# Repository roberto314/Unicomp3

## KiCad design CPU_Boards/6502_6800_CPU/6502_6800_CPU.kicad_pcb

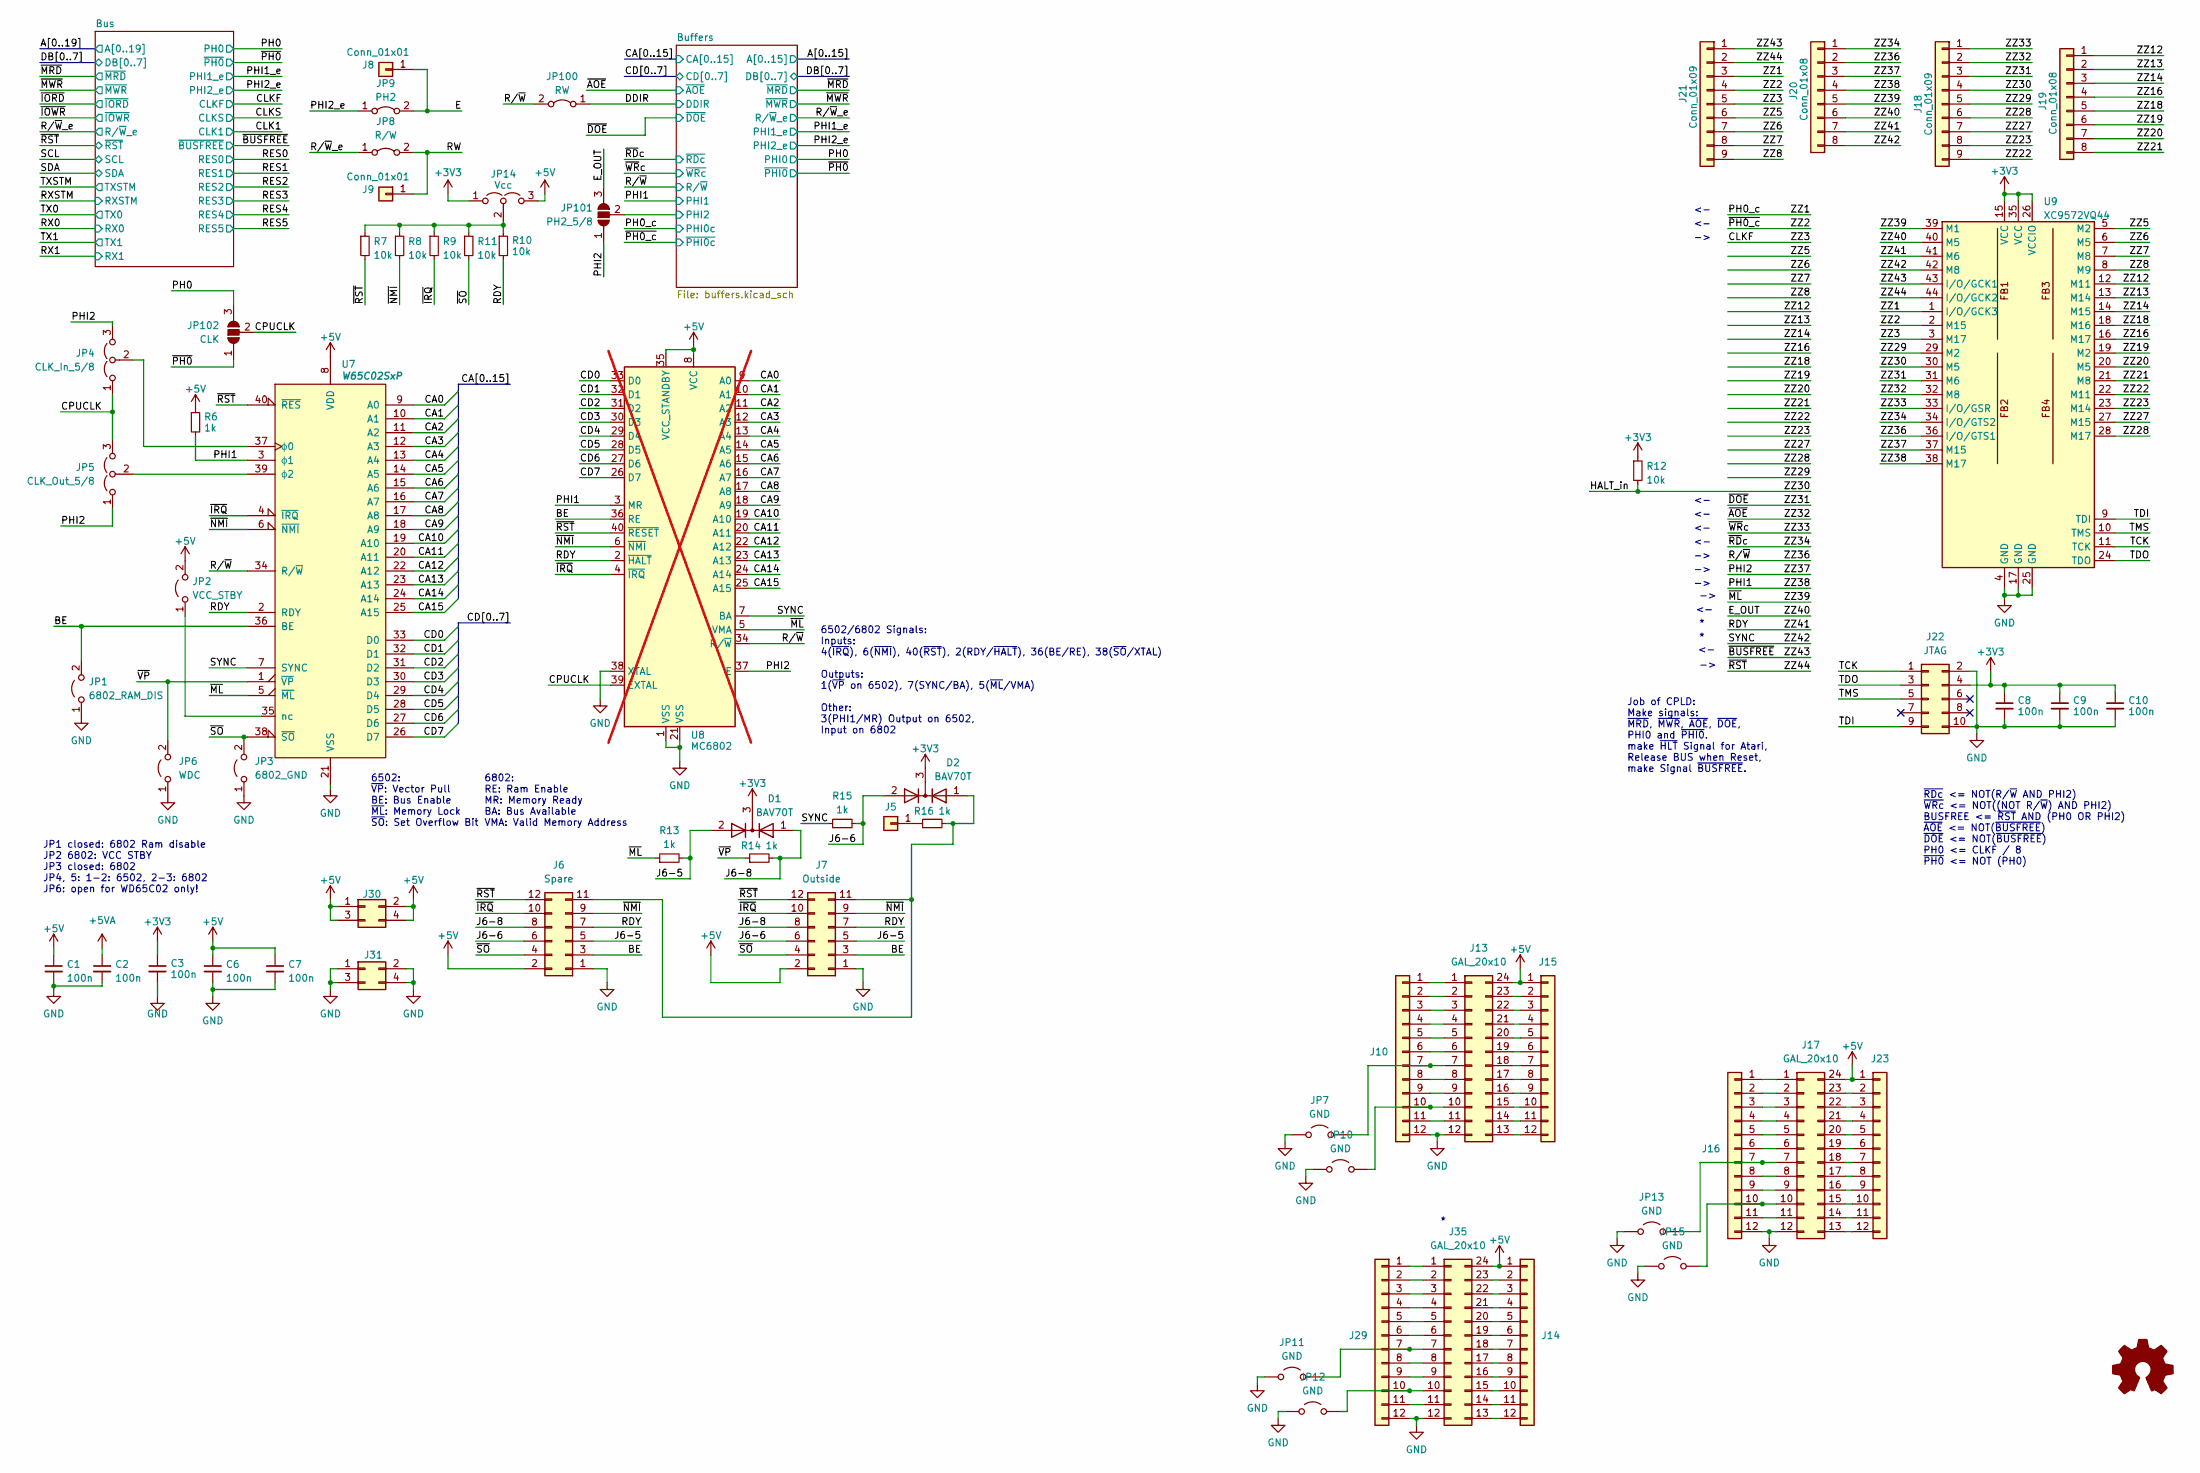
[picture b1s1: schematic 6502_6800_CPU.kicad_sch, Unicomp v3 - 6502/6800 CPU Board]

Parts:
C1, C2, C3, C6, C7, C8, C9, C10: 100n; C_1206_3216Metric
D1, D2: BAV70T; SOT-23_Handsoldering
J5: Conn_01x01; PinSocket_1x01_P1.27mm_Vertical
J6: Spare; PinHeader_2x06_P2.54mm_Vertical
J7: Outside; PinHeader_2x06_P2.54mm_Horizontal
J8, J9: Conn_01x01; PinHeader_1x01_P2.00mm_Vertical
J10, J14, J15, J16, J23, J29: Conn_01x12; PinSocket_1x12_P2.54mm_Vertical
J13, J17, J35: GAL_20x10; DIP-24_W7.62mm
J18, J21: Conn_01x09; PinHeader_1x09_P2.54mm_Vertical
J19, J20: Conn_01x08; PinHeader_1x08_P2.54mm_Vertical
J22: JTAG; PinHeader_2x05_P2.54mm_Horizontal
J30, J31: Conn_02x02_Odd_Even; PinSocket_2x02_P2.54mm_Vertical
JP1: 6802_RAM_DIS; SolderJumper-2_P1.3mm_Open_RoundedPad1.0x1.5mm
JP2: VCC_STBY; SolderJumper-2_P1.3mm_Open_RoundedPad1.0x1.5mm
JP3: 6802_GND; SolderJumper-2_P1.3mm_Open_RoundedPad1.0x1.5mm
JP4: CLK_In_5/8; SolderJumper-3_P1.3mm_Open_Pad1.0x1.5mm_NumberLabels
JP5: CLK_Out_5/8; SolderJumper-3_P1.3mm_Open_Pad1.0x1.5mm_NumberLabels
JP6: WDC; SolderJumper-2_P1.3mm_Open_RoundedPad1.0x1.5mm
JP7, JP10, JP11, JP12, JP13, JP15: GND; SolderJumper-2_P1.3mm_Open_RoundedPad1.0x1.5mm
JP8: R/W; SolderJumper-2_P1.3mm_Bridged_RoundedPad1.0x1.5mm
JP9: PH2; SolderJumper-2_P1.3mm_Bridged_RoundedPad1.0x1.5mm
JP14: Vcc; SolderJumper-3_P1.3mm_Open_RoundedPad1.0x1.5mm_NumberLabels
JP100: RW; SolderJumper-2_P1.3mm_Bridged_RoundedPad1.0x1.5mm
JP101: PH2_5/8; SolderJumper-3_P1.3mm_Open_RoundedPad1.0x1.5mm_NumberLabels
JP102: CLK; SolderJumper-3_P1.3mm_Open_RoundedPad1.0x1.5mm_NumberLabels
R6, R13, R14, R15, R16: 1k; R_1206_3216Metric_Pad1.30x1.75mm_HandSolder
R7, R8, R9, R10, R11, R12: 10k; R_1206_3216Metric_Pad1.30x1.75mm_HandSolder
U7: W65C02SxP; DIP-40_W15.24mm_Socket_LongPads
U8: MC6802; DIP-40_W15.24mm; not fitted
U9: XC9572VQ44; TQFP-44_10x10mm_P0.8mm

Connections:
+3V3: C3.1, C8.1, C9.1, C10.1, D1.3 (K), D2.3 (K), J22.4, JP14.1 (A), R12.1, U9.15 (VCC), U9.26 (VCCIO), U9.35 (VCC); also elsewhere on the board
+5V: C1.1, C6.1, C7.1, J6.2, J7.2, J13.24, J14.1, J15.1, J17.24, J23.1, J30.1, J30.2, J30.3, J30.4, J35.24, JP2.2 (B), JP14.3 (B), R6.1, U7.8 (VDD), U8.8 (VCC), U8.35 (VCC_STANDBY); also elsewhere on the board
+5VA: C2.1; also elsewhere on the board
/BE: J6.3, J7.3, JP1.2 (B), U7.36 (BE), U8.36 (RE)
/Buffers/PHI2: JP101.2 (C); also elsewhere on the board
/CA0: U7.9 (A0), U8.9 (A0); also elsewhere on the board
/CA1: U7.10 (A1), U8.10 (A1); also elsewhere on the board
/CA2: U7.11 (A2), U8.11 (A2); also elsewhere on the board
/CA3: U7.12 (A3), U8.12 (A3); also elsewhere on the board
/CA4: U7.13 (A4), U8.13 (A4); also elsewhere on the board
/CA5: U7.14 (A5), U8.14 (A5); also elsewhere on the board
/CA6: U7.15 (A6), U8.15 (A6); also elsewhere on the board
/CA7: U7.16 (A7), U8.16 (A7); also elsewhere on the board
/CA8: U7.17 (A8), U8.17 (A8); also elsewhere on the board
/CA9: U7.18 (A9), U8.18 (A9); also elsewhere on the board
/CA10: U7.19 (A10), U8.19 (A10); also elsewhere on the board
/CA11: U7.20 (A11), U8.20 (A11); also elsewhere on the board
/CA12: U7.22 (A12), U8.22 (A12); also elsewhere on the board
/CA13: U7.23 (A13), U8.23 (A13); also elsewhere on the board
/CA14: U7.24 (A14), U8.24 (A14); also elsewhere on the board
/CA15: U7.25 (A15), U8.25 (A15); also elsewhere on the board
/CD0: U7.33 (D0), U8.33 (D0); also elsewhere on the board
/CD1: U7.32 (D1), U8.32 (D1); also elsewhere on the board
/CD2: U7.31 (D2), U8.31 (D2); also elsewhere on the board
/CD3: U7.30 (D3), U8.30 (D3); also elsewhere on the board
/CD4: U7.29 (D4), U8.29 (D4); also elsewhere on the board
/CD5: U7.28 (D5), U8.28 (D5); also elsewhere on the board
/CD6: U7.27 (D6), U8.27 (D6); also elsewhere on the board
/CD7: U7.26 (D7), U8.26 (D7); also elsewhere on the board
/CLKF: J21.5, U9.3 (M17); also elsewhere on the board
/CPUCLK: JP4.1 (A), JP5.3 (B), JP102.2 (C), U8.39 (EXTAL)
/DDIR: JP100.1 (A); also elsewhere on the board
/E: J8.1, JP9.2 (B)
/E_OUT: J20.6, JP101.3 (B), U9.40 (M5)
/HALT_in: J18.4, R12.2, U9.30 (M5)
/J6-5: D1.2 (A), J6.5, J7.5, R13.2
/J6-6: D2.2 (A), J6.6, J7.6, R15.2
/J6-8: D1.1 (A), J6.8, J7.8, R14.2
/PH0: JP102.3 (B); also elsewhere on the board
/PH0_c: J21.3, U9.1 (I/O/GCK3); also elsewhere on the board
/PHI1: J20.4, R6.2, U7.3 (ϕ1), U8.3 (MR), U9.38 (M17); also elsewhere on the board
/PHI2: J20.3, JP4.3 (B), JP5.1 (A), JP101.1 (A), U8.37 (E), U9.37 (M15)
/PHI2_e: JP9.1 (A); also elsewhere on the board
/RDY: J6.7, J7.7, J20.7, R10.2, U7.2 (RDY), U8.2 (~HALT), U9.41 (M6)
/RW: J9.1, JP8.2 (B)
/R/~W: J20.2, JP100.2 (B), U7.34 (R/~W), U8.34 (R/~W), U9.36 (I/O/GTS1); also elsewhere on the board
/R/~W_e: JP8.1 (A); also elsewhere on the board
/SYNC: J20.8, R15.1, U7.7 (SYNC), U8.7 (BA), U9.42 (M8)
/TCK: J22.1, U9.11 (TCK)
/TDI: J22.9, U9.9 (TDI)
/TDO: J22.3, U9.24 (TDO)
/TMS: J22.5, U9.10 (TMS)
/ZZ2: J21.4, U9.2 (M15); also elsewhere on the board
/ZZ5: J21.6, U9.5 (M2)
/ZZ6: J21.7, U9.6 (M5)
/ZZ7: J21.8, U9.7 (M8)
/ZZ8: J21.9, U9.8 (M9)
/ZZ12: J19.1, U9.12 (M11)
/ZZ13: J19.2, U9.13 (M14)
/ZZ14: J19.3, U9.14 (M15)
/ZZ16: J19.4, U9.16 (M17)
/ZZ18: J19.5, U9.18 (M16)
/ZZ19: J19.6, U9.19 (M2)
/ZZ20: J19.7, U9.20 (M5)
/ZZ21: J19.8, U9.21 (M8)
/ZZ22: J18.9, U9.22 (M11)
/ZZ23: J18.8, U9.23 (M14)
/ZZ27: J18.7, U9.27 (M15)
/ZZ28: J18.6, U9.28 (M17)
/ZZ29: J18.5, U9.29 (M2)
/ZZ31: J18.3, U9.31 (M6); also elsewhere on the board
/ZZ32: J18.2, U9.32 (M8); also elsewhere on the board
/ZZ33: J18.1, U9.33 (I/O/GSR); also elsewhere on the board
/ZZ34: J20.1, U9.34 (I/O/GTS2); also elsewhere on the board
/ZZ39: J20.5, R13.1, U7.5 (~ML), U8.5 (VMA), U9.39 (M1)
/ZZ43: J21.1, U9.43 (I/O/GCK1); also elsewhere on the board
/ZZ44: J6.12, J7.12, J21.2, R7.2, U7.40 (~RES), U8.40 (~RESET), U9.44 (I/O/GCK2); also elsewhere on the board
/~IRQ: J6.10, J7.10, R9.2, U7.4 (~IRQ), U8.4 (~IRQ)
/~NMI: J6.9, J7.9, R8.2, U7.6 (~NMI), U8.6 (~NMI)
/~PH0: JP102.1 (A); also elsewhere on the board
/~SO: J6.4, J7.4, JP3.2 (B), R11.2, U7.38 (~SO)
/~VP: JP6.2 (B), R14.1, U7.1 (~VP)
GND: C1.2, C2.2, C3.2, C6.2, C7.2, C8.2, C9.2, C10.2, J6.1, J7.1, J10.12, J13.12, J16.12, J17.12, J22.2, J22.10, J29.12, J31.1, J31.2, J31.3, J31.4, J35.12, JP1.1 (A), JP3.1 (A), JP6.1 (A), JP7.1 (A), JP10.1 (A), JP11.1 (A), JP12.1 (A), JP13.1 (A), JP15.1 (A), U7.21 (VSS), U8.1 (VSS), U8.21 (VSS), U8.38 (XTAL), U9.4 (GND), U9.17 (GND), U9.25 (GND); also elsewhere on the board
unnamed: J5.1, R16.1
unnamed: D2.1 (A), J6.11, J7.11, R16.2
unnamed: J10.1, J13.1
unnamed: J10.2, J13.2
unnamed: J10.3, J13.3
unnamed: J10.4, J13.4
unnamed: J10.5, J13.5
unnamed: J10.6, J13.6
unnamed: J10.7, J13.7, JP7.2 (B)
unnamed: J10.8, J13.8
unnamed: J10.9, J13.9
unnamed: J10.10, J13.10, JP10.2 (B)
unnamed: J10.11, J13.11
unnamed: J13.13, J15.12
unnamed: J13.14, J15.11
unnamed: J13.15, J15.10
unnamed: J13.16, J15.9
unnamed: J13.17, J15.8
unnamed: J13.18, J15.7
unnamed: J13.19, J15.6
unnamed: J13.20, J15.5
unnamed: J13.21, J15.4
unnamed: J13.22, J15.3
unnamed: J13.23, J15.2
unnamed: J14.2, J35.23
unnamed: J14.3, J35.22
unnamed: J14.4, J35.21
unnamed: J14.5, J35.20
unnamed: J14.6, J35.19
unnamed: J14.7, J35.18
unnamed: J14.8, J35.17
unnamed: J14.9, J35.16
unnamed: J14.10, J35.15
unnamed: J14.11, J35.14
unnamed: J14.12, J35.13
unnamed: J16.1, J17.1
unnamed: J16.2, J17.2
unnamed: J16.3, J17.3
unnamed: J16.4, J17.4
unnamed: J16.5, J17.5
unnamed: J16.6, J17.6
unnamed: J16.7, J17.7, JP13.2 (B)
unnamed: J16.8, J17.8
unnamed: J16.9, J17.9
unnamed: J16.10, J17.10, JP15.2 (B)
unnamed: J16.11, J17.11
unnamed: J17.13, J23.12
unnamed: J17.14, J23.11
unnamed: J17.15, J23.10
unnamed: J17.16, J23.9
unnamed: J17.17, J23.8
unnamed: J17.18, J23.7
unnamed: J17.19, J23.6
unnamed: J17.20, J23.5
unnamed: J17.21, J23.4
unnamed: J17.22, J23.3
unnamed: J17.23, J23.2
unnamed: J29.1, J35.1
unnamed: J29.2, J35.2
unnamed: J29.3, J35.3
unnamed: J29.4, J35.4
unnamed: J29.5, J35.5
unnamed: J29.6, J35.6
unnamed: J29.7, J35.7, JP11.2 (B)
unnamed: J29.8, J35.8
unnamed: J29.9, J35.9
unnamed: J29.10, J35.10, JP12.2 (B)
unnamed: J29.11, J35.11
unnamed: JP2.1 (A), U7.35 (nc)
unnamed: JP4.2 (C), U7.37 (ϕ0)
unnamed: JP5.2 (C), U7.39 (ϕ2)
unnamed: JP14.2 (C), R7.1, R8.1, R9.1, R10.1, R11.1

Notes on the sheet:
6502/6802 Signals: Inputs: 4(~{IRQ}), 6(~{NMI}), 40(~{RST}), 2(RDY/~{HALT}), 36(BE/RE), 38(~{SO}/XTAL) Outputs: 1(~{VP} on 6502), 7(SYNC/BA), 5(~{ML}/VMA) Other: 3(PHI1/MR) Output on 6502, Input on 6802
JP1 closed: 6802 Ram disable JP2 6802: VCC STBY JP3 closed: 6802 JP4, 5: 1-2: 6502, 2-3: 6802 JP6: open for WD65C02 only!
6502: ~{VP}: Vector Pull BE: Bus Enable ~{ML}: Memory Lock ~{SO}: Set Overflow Bit
Job of CPLD: Make signals: ~{MRD}, ~{MWR}, ~{AOE}, ~{DOE}, PHI0 and ~{PHI0}. make ~{HLT} Signal for Atari, Release BUS when Reset, make Signal ~{BUSFREE}.
~{RDc} <= NOT(R/~{W} AND PHI2) ~{WRc} <= NOT((NOT R/~{W}) AND PHI2) BUSFREE <= ~{RST} AND (PH0 OR PHI2) ~{AOE} <= NOT(~{BUSFREE}) ~{DOE} <= NOT(~{BUSFREE}) PH0 <= CLKF / 8 ~{PH0} <= NOT (PH0)
6802: RE: Ram Enable MR: Memory Ready BA: Bus Available VMA: Valid Memory Address

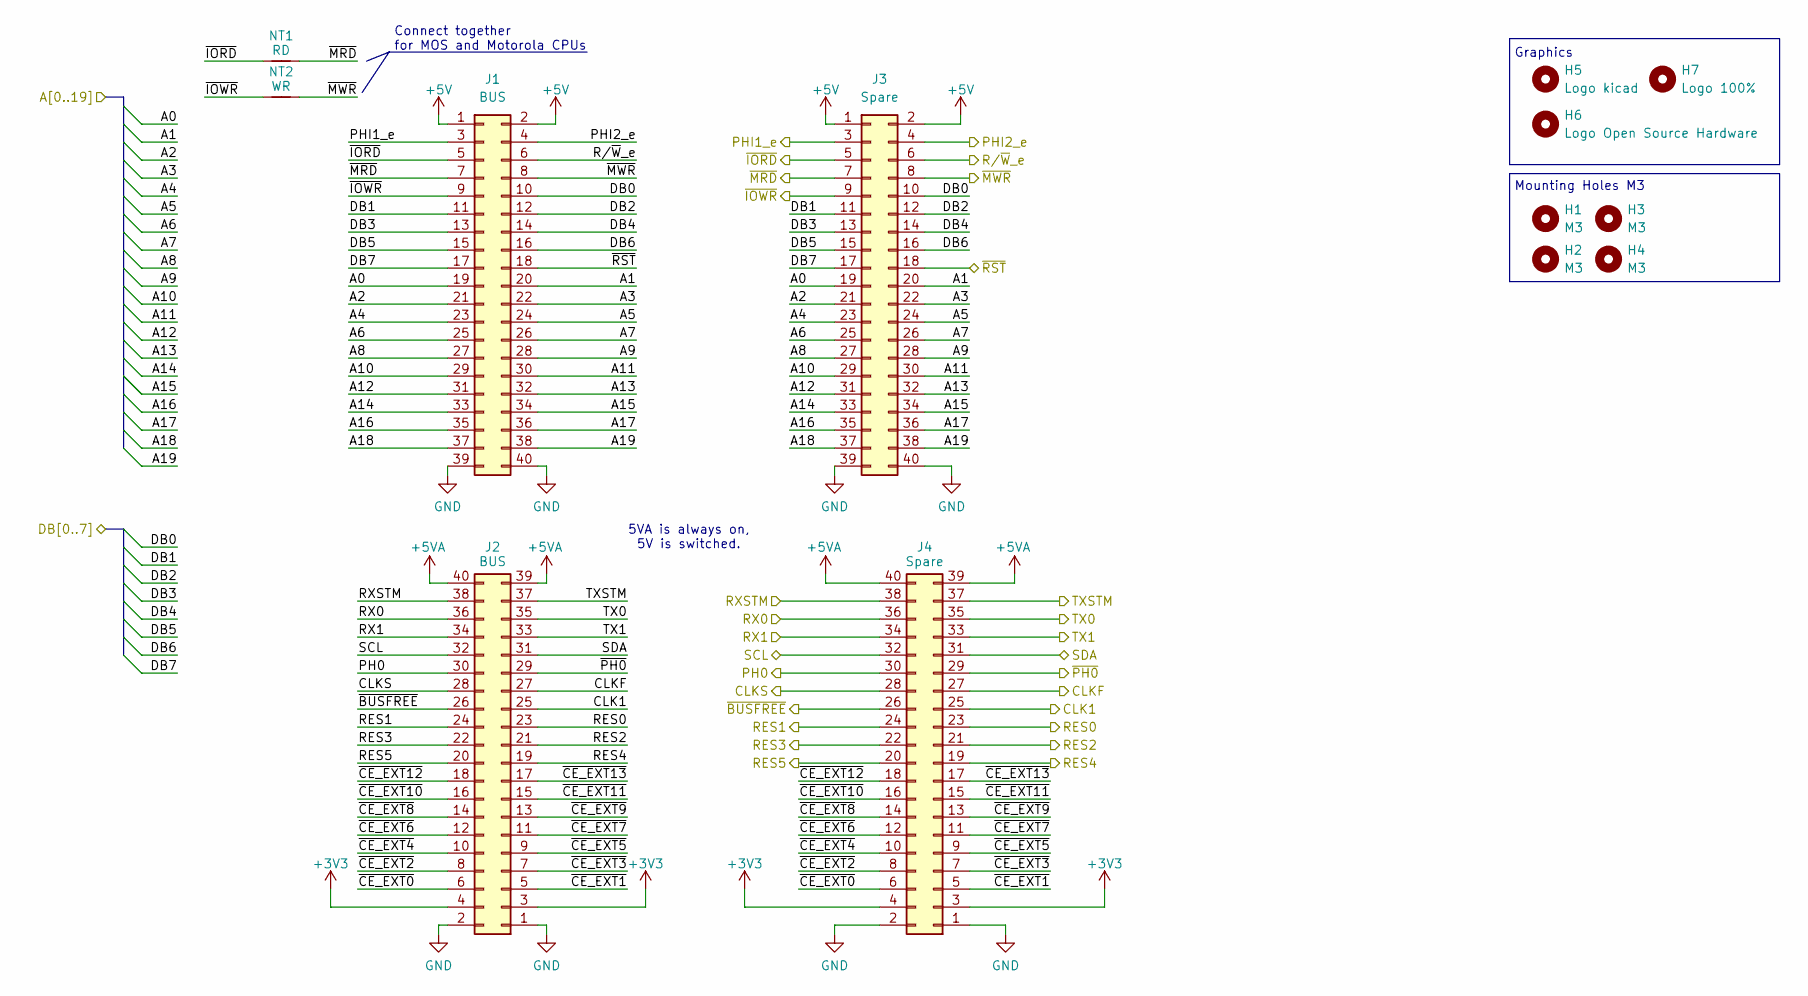
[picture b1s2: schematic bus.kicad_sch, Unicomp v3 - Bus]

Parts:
H1, H2, H3, H4: M3; MountingHole_3.2mm_M3
H5: Logo kicad; KiCad-Logo2_6mm_SilkScreen
H6: Logo Open Source Hardware; OSHW-Logo2_7.3x6mm_SilkScreen
H7: Logo 100%; Logo_100ProzentOffner_10x2.7mm
J1, J2: BUS; PinSocket_2x20_P2.54mm_Vertical
J3, J4: Spare; PinSocket_2x20_P2.54mm_Vertical
NT1: RD; NetTie-2_SMD_Pad0.5mm
NT2: WR; NetTie-2_SMD_Pad0.5mm

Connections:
+3V3: J2.3, J2.4, J4.3, J4.4; also elsewhere on the board
+5V: J1.1, J1.2, J3.1, J3.2; also elsewhere on the board
+5VA: J2.39, J2.40, J4.39, J4.40; also elsewhere on the board
/A0: J1.19, J3.19; also elsewhere on the board
/A1: J1.20, J3.20; also elsewhere on the board
/A2: J1.21, J3.21; also elsewhere on the board
/A3: J1.22, J3.22; also elsewhere on the board
/A4: J1.23, J3.23; also elsewhere on the board
/A5: J1.24, J3.24; also elsewhere on the board
/A6: J1.25, J3.25; also elsewhere on the board
/A7: J1.26, J3.26; also elsewhere on the board
/A8: J1.27, J3.27; also elsewhere on the board
/A9: J1.28, J3.28; also elsewhere on the board
/A10: J1.29, J3.29; also elsewhere on the board
/A11: J1.30, J3.30; also elsewhere on the board
/A12: J1.31, J3.31; also elsewhere on the board
/A13: J1.32, J3.32; also elsewhere on the board
/A14: J1.33, J3.33; also elsewhere on the board
/A15: J1.34, J3.34; also elsewhere on the board
/A16: J1.35, J3.35
/A17: J1.36, J3.36
/A18: J1.37, J3.37
/A19: J1.38, J3.38
/Bus/~CE_EXT0: J2.6, J4.6
/Bus/~CE_EXT1: J2.5, J4.5
/Bus/~CE_EXT2: J2.8, J4.8
/Bus/~CE_EXT3: J2.7, J4.7
/Bus/~CE_EXT4: J2.10, J4.10
/Bus/~CE_EXT5: J2.9, J4.9
/Bus/~CE_EXT6: J2.12, J4.12
/Bus/~CE_EXT7: J2.11, J4.11
/Bus/~CE_EXT8: J2.14, J4.14
/Bus/~CE_EXT9: J2.13, J4.13
/Bus/~CE_EXT10: J2.16, J4.16
/Bus/~CE_EXT11: J2.15, J4.15
/Bus/~CE_EXT12: J2.18, J4.18
/Bus/~CE_EXT13: J2.17, J4.17
/CLK1: J2.25, J4.25
/CLKF: J2.27, J4.27; also elsewhere on the board
/CLKS: J2.28, J4.28
/DB0: J1.10, J3.10; also elsewhere on the board
/DB1: J1.11, J3.11; also elsewhere on the board
/DB2: J1.12, J3.12; also elsewhere on the board
/DB3: J1.13, J3.13; also elsewhere on the board
/DB4: J1.14, J3.14; also elsewhere on the board
/DB5: J1.15, J3.15; also elsewhere on the board
/DB6: J1.16, J3.16; also elsewhere on the board
/DB7: J1.17, J3.17; also elsewhere on the board
/PH0: J2.30, J4.30; also elsewhere on the board
/PHI1_e: J1.3, J3.3; also elsewhere on the board
/PHI2_e: J1.4, J3.4; also elsewhere on the board
/RES0: J2.23, J4.23
/RES1: J2.24, J4.24
/RES2: J2.21, J4.21
/RES3: J2.22, J4.22
/RES4: J2.19, J4.19
/RES5: J2.20, J4.20
/RX0: J2.36, J4.36
/RX1: J2.34, J4.34
/RXSTM: J2.38, J4.38
/R/~W_e: J1.6, J3.6; also elsewhere on the board
/SCL: J2.32, J4.32
/SDA: J2.31, J4.31
/TX0: J2.35, J4.35
/TX1: J2.33, J4.33
/TXSTM: J2.37, J4.37
/ZZ43: J2.26, J4.26; also elsewhere on the board
/ZZ44: J1.18, J3.18; also elsewhere on the board
/~IORD: J1.5, J3.5, NT1.1
/~IOWR: J1.9, J3.9, NT2.1
/~MRD: J1.7, J3.7, NT1.2; also elsewhere on the board
/~MWR: J1.8, J3.8, NT2.2; also elsewhere on the board
/~PH0: J2.29, J4.29; also elsewhere on the board
GND: J1.39, J1.40, J2.1, J2.2, J3.39, J3.40, J4.1, J4.2; also elsewhere on the board

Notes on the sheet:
Graphics
Connect together for MOS and Motorola CPUs
5VA is always on, 5V is switched.
Mounting Holes M3

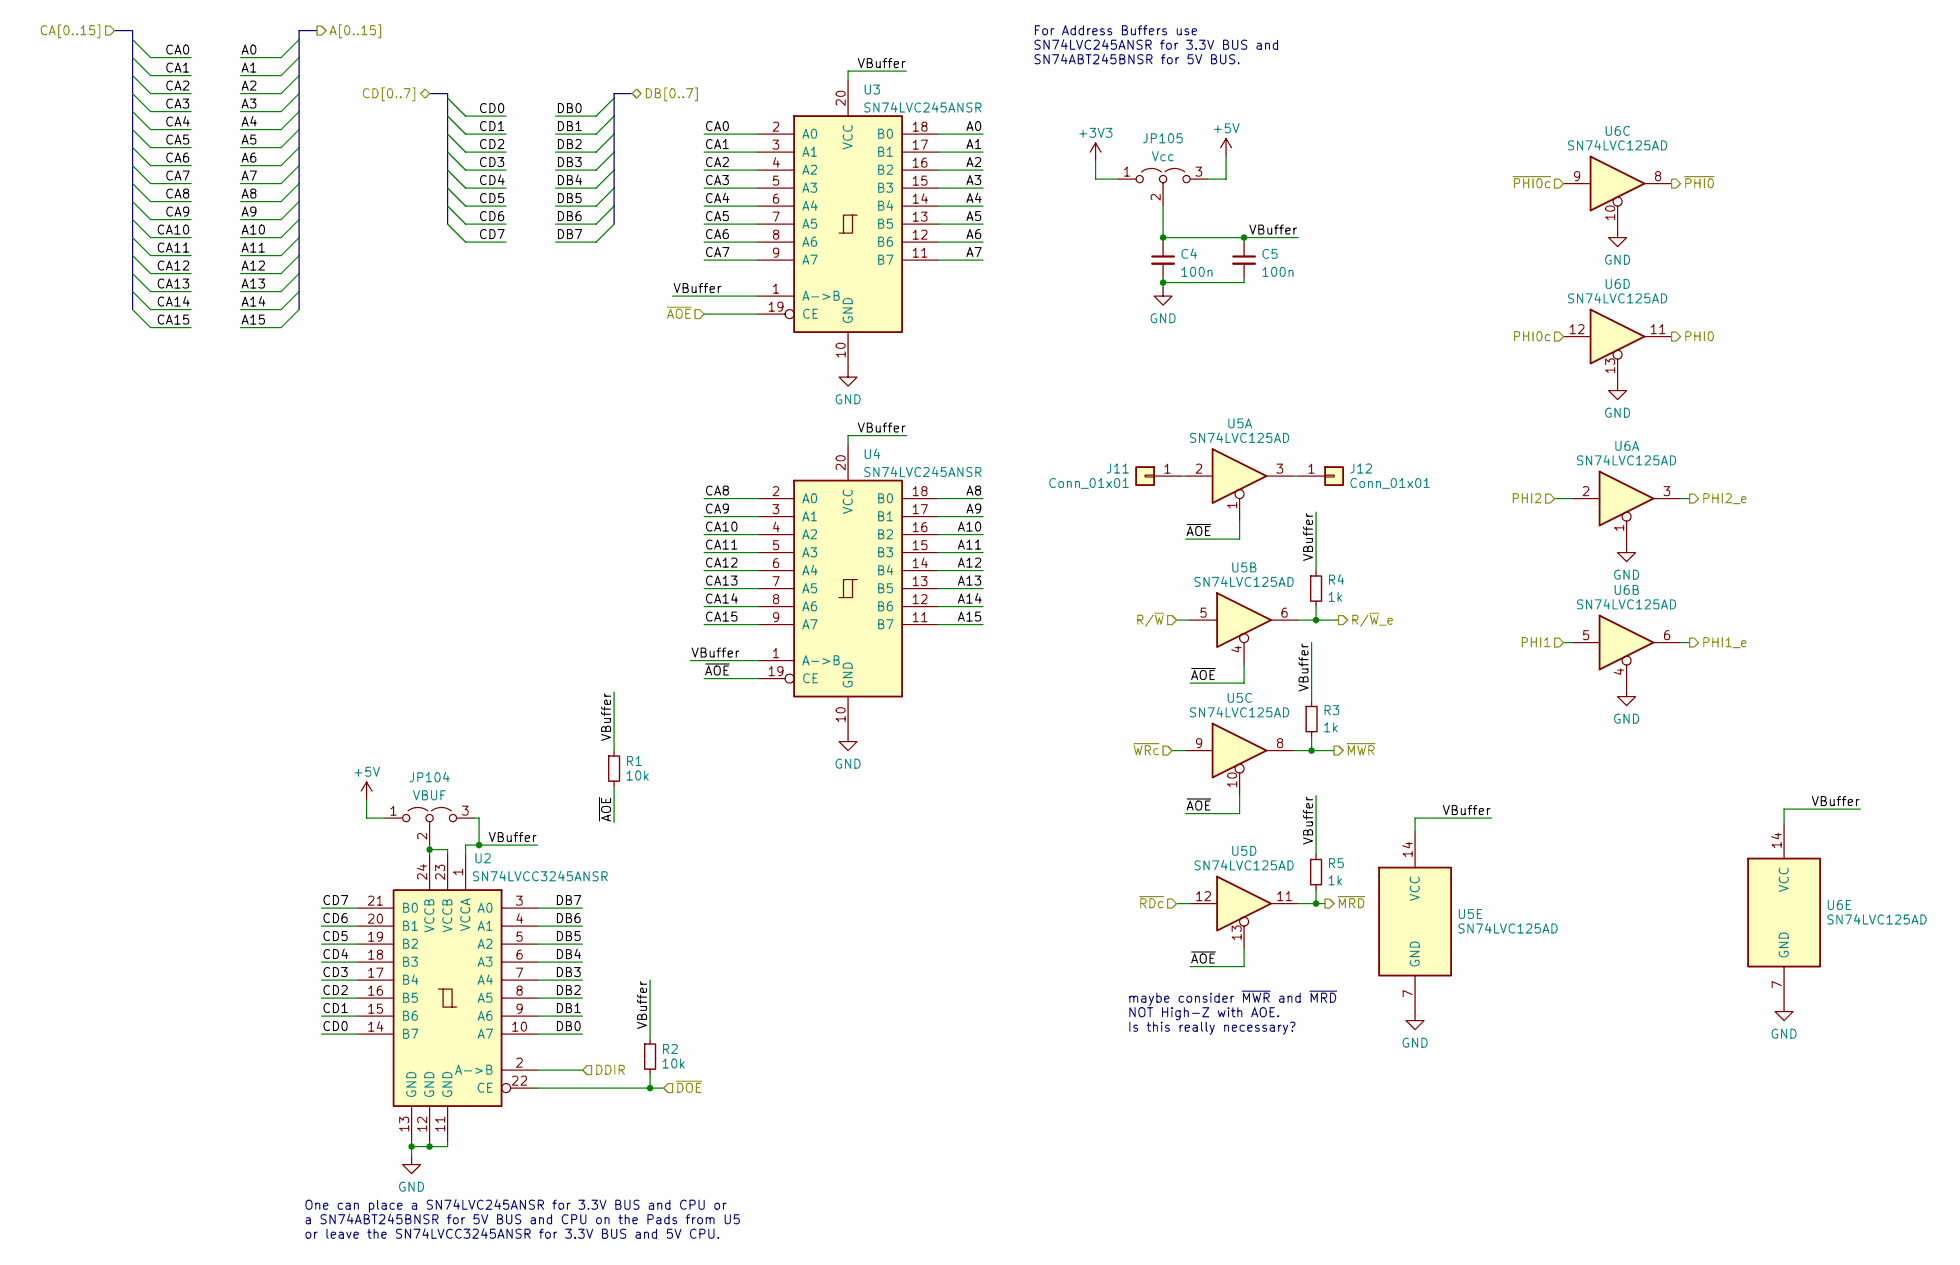
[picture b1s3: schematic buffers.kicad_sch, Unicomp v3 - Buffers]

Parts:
C4, C5: 100n; C_1206_3216Metric
J11, J12: Conn_01x01; PinHeader_1x01_P1.27mm_Vertical
JP104: VBUF; SolderJumper-3_P1.3mm_Open_Pad1.0x1.5mm_NumberLabels
JP105: Vcc; SolderJumper-3_P1.3mm_Open_RoundedPad1.0x1.5mm_NumberLabels
R1, R2: 10k; R_1206_3216Metric_Pad1.30x1.75mm_HandSolder
R3, R4, R5: 1k; R_1206_3216Metric_Pad1.30x1.75mm_HandSolder
U2: SN74LVCC3245ANSR; SO-24_5.3x15mm_P1.27mm
U3, U4: SN74LVC245ANSR; SO-20_5.3x12.6mm_P1.27mm
U5, U6: SN74LVC125AD; SOIC-14_3.9x8.7mm_P1.27mm

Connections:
+3V3: JP105.1 (A); also elsewhere on the board
+5V: JP104.1 (A), JP105.3 (B); also elsewhere on the board
/A0: U3.18 (B0); also elsewhere on the board
/A1: U3.17 (B1); also elsewhere on the board
/A2: U3.16 (B2); also elsewhere on the board
/A3: U3.15 (B3); also elsewhere on the board
/A4: U3.14 (B4); also elsewhere on the board
/A5: U3.13 (B5); also elsewhere on the board
/A6: U3.12 (B6); also elsewhere on the board
/A7: U3.11 (B7); also elsewhere on the board
/A8: U4.18 (B0); also elsewhere on the board
/A9: U4.17 (B1); also elsewhere on the board
/A10: U4.16 (B2); also elsewhere on the board
/A11: U4.15 (B3); also elsewhere on the board
/A12: U4.14 (B4); also elsewhere on the board
/A13: U4.13 (B5); also elsewhere on the board
/A14: U4.12 (B6); also elsewhere on the board
/A15: U4.11 (B7); also elsewhere on the board
/Buffers/PHI2: U6.2; also elsewhere on the board
/Buffers/VBuffer: C4.1, C5.1, JP104.3 (B), JP105.2 (C), R1.1, R2.1, R3.1, R4.1, R5.1, U2.1 (VCCA), U3.1 (A->B), U3.20 (VCC), U4.1 (A->B), U4.20 (VCC), U5.14 (VCC), U6.14 (VCC)
/CA0: U3.2 (A0); also elsewhere on the board
/CA1: U3.3 (A1); also elsewhere on the board
/CA2: U3.4 (A2); also elsewhere on the board
/CA3: U3.5 (A3); also elsewhere on the board
/CA4: U3.6 (A4); also elsewhere on the board
/CA5: U3.7 (A5); also elsewhere on the board
/CA6: U3.8 (A6); also elsewhere on the board
/CA7: U3.9 (A7); also elsewhere on the board
/CA8: U4.2 (A0); also elsewhere on the board
/CA9: U4.3 (A1); also elsewhere on the board
/CA10: U4.4 (A2); also elsewhere on the board
/CA11: U4.5 (A3); also elsewhere on the board
/CA12: U4.6 (A4); also elsewhere on the board
/CA13: U4.7 (A5); also elsewhere on the board
/CA14: U4.8 (A6); also elsewhere on the board
/CA15: U4.9 (A7); also elsewhere on the board
/CD0: U2.14 (B7); also elsewhere on the board
/CD1: U2.15 (B6); also elsewhere on the board
/CD2: U2.16 (B5); also elsewhere on the board
/CD3: U2.17 (B4); also elsewhere on the board
/CD4: U2.18 (B3); also elsewhere on the board
/CD5: U2.19 (B2); also elsewhere on the board
/CD6: U2.20 (B1); also elsewhere on the board
/CD7: U2.21 (B0); also elsewhere on the board
/DB0: U2.10 (A7); also elsewhere on the board
/DB1: U2.9 (A6); also elsewhere on the board
/DB2: U2.8 (A5); also elsewhere on the board
/DB3: U2.7 (A4); also elsewhere on the board
/DB4: U2.6 (A3); also elsewhere on the board
/DB5: U2.5 (A2); also elsewhere on the board
/DB6: U2.4 (A1); also elsewhere on the board
/DB7: U2.3 (A0); also elsewhere on the board
/DDIR: U2.2 (A->B); also elsewhere on the board
/PH0: U6.11; also elsewhere on the board
/PH0_c: U6.12; also elsewhere on the board
/PHI1: U6.5; also elsewhere on the board
/PHI1_e: U6.6; also elsewhere on the board
/PHI2_e: U6.3; also elsewhere on the board
/R/~W: U5.5; also elsewhere on the board
/R/~W_e: R4.2, U5.6; also elsewhere on the board
/ZZ2: U6.9; also elsewhere on the board
/ZZ31: R2.2, U2.22 (CE); also elsewhere on the board
/ZZ32: R1.2, U3.19 (CE), U4.19 (CE), U5.1, U5.4, U5.10, U5.13; also elsewhere on the board
/ZZ33: U5.9; also elsewhere on the board
/ZZ34: U5.12; also elsewhere on the board
/~MRD: R5.2, U5.11; also elsewhere on the board
/~MWR: R3.2, U5.8; also elsewhere on the board
/~PH0: U6.8; also elsewhere on the board
GND: C4.2, C5.2, U2.11 (GND), U2.12 (GND), U2.13 (GND), U3.10 (GND), U4.10 (GND), U5.7 (GND), U6.1, U6.4, U6.7 (GND), U6.10, U6.13; also elsewhere on the board
unnamed: J11.1, U5.2
unnamed: J12.1, U5.3
unnamed: JP104.2 (C), U2.23 (VCCB), U2.24 (VCCB)

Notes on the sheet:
For Address Buffers use SN74LVC245ANSR for 3.3V BUS and SN74ABT245BNSR for 5V BUS.
One can place a SN74LVC245ANSR for 3.3V BUS and CPU or a SN74ABT245BNSR for 5V BUS and CPU on the Pads from U5 or leave the SN74LVCC3245ANSR for 3.3V BUS and 5V CPU.
maybe consider ~{MWR} and ~{MRD} NOT High-Z with AOE. Is this really necessary?

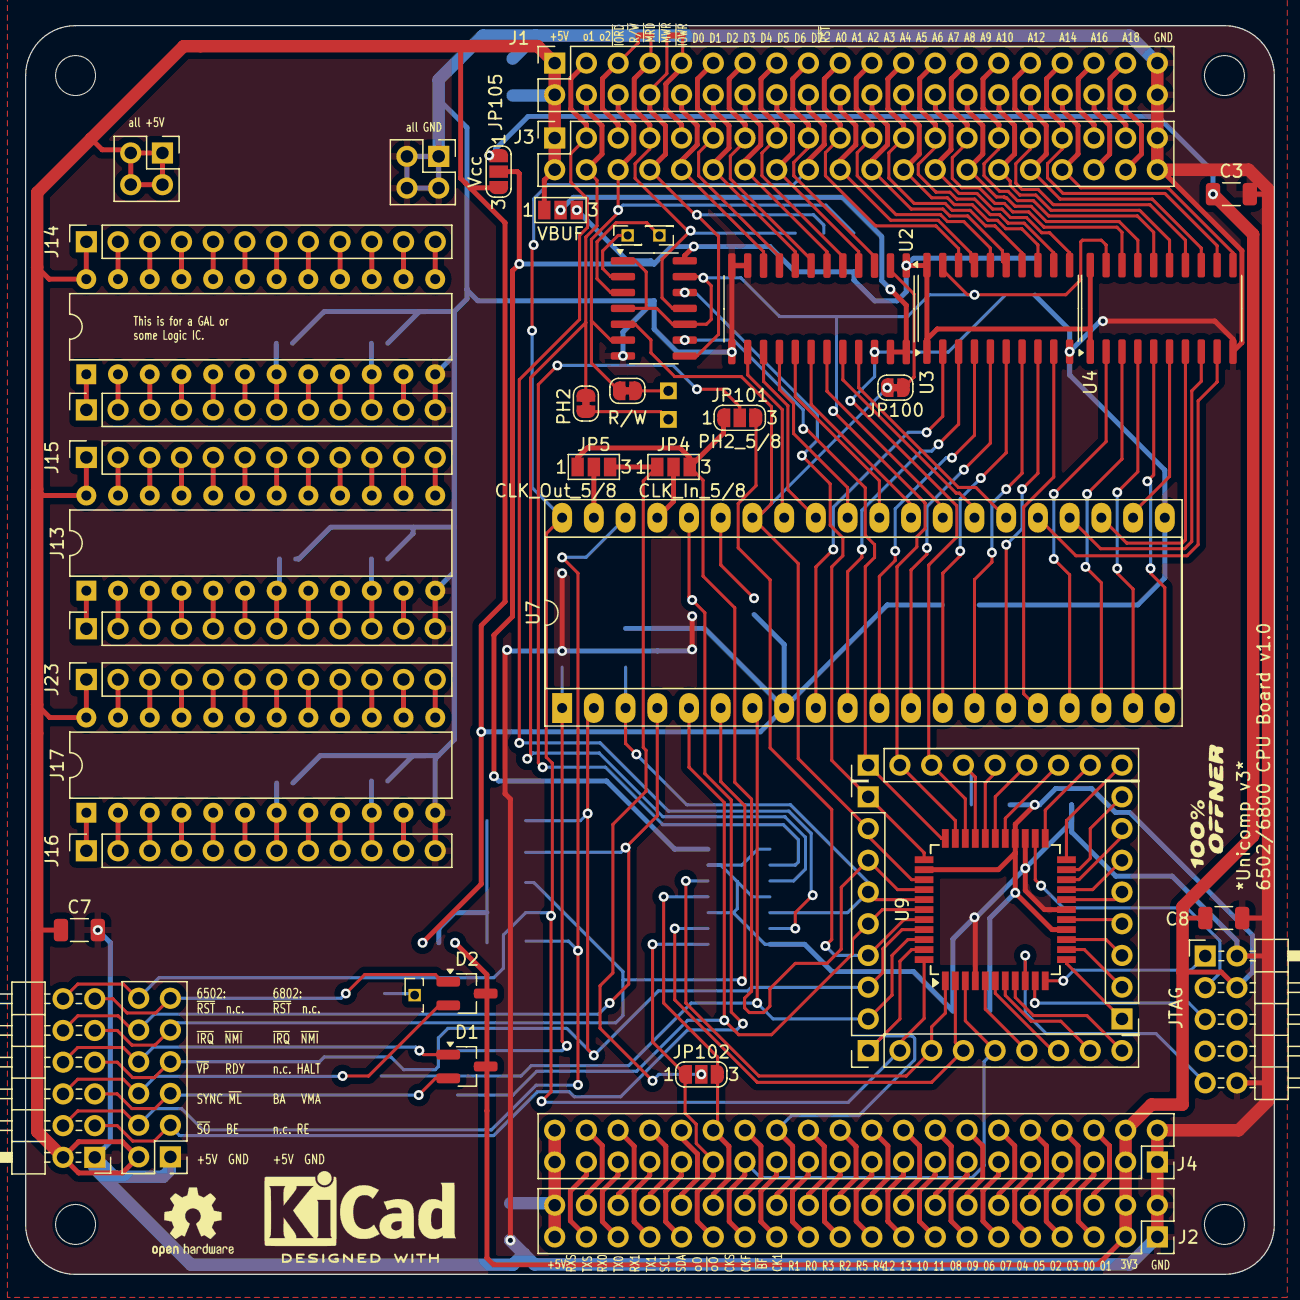
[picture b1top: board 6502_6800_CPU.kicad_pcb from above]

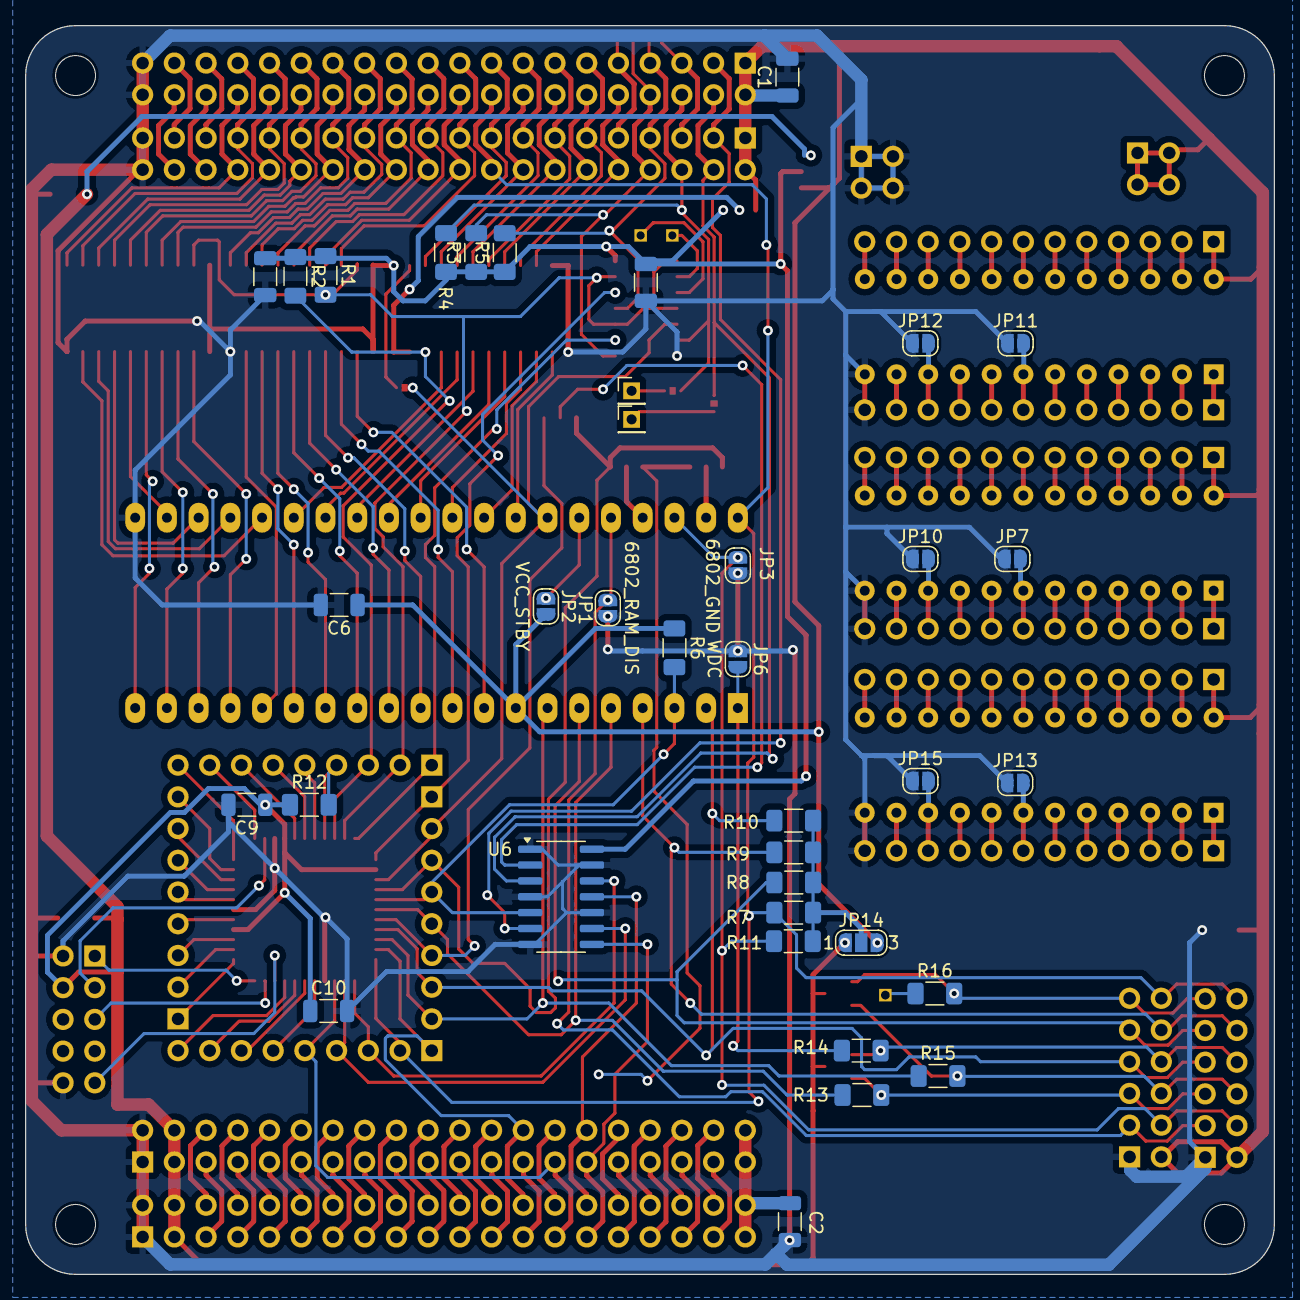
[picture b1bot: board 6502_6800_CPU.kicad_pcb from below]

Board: 2 copper layers, 100.0 x 100.0 mm, 91 parts (37 on the bottom side), 222 nets.
